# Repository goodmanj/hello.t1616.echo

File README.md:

# hello.t1616.echo
 
This is a version of the ["hello.echo"](http://academy.cba.mit.edu/classes/embedded_programming/index.html#echo) board for Week 6 of Fab Academy, designed for the ATTiny1616 microcontroller.  This particular chip is not included in Neil Gershenfeld's "hello.echo" boards, and we happen to have a lot of them.

Program using Spence Konde's [megaTinyCore](https://github.com/SpenceKonde/megaTinyCore) for Arduino, and a [pyUPDI-style](https://github.com/SpenceKonde/megaTinyCore/blob/master/MakeUPDIProgrammer.md) FTDI-to-UDPI adapter.

Materials:
* 1 uF 1206 SMD capacitor
* SOIC-20W ATTiny1616-S
* 1x6 2.54 mm pitch horizontal male SMD header
* 1x3 2.54 mm pitch horizontal male SMD header

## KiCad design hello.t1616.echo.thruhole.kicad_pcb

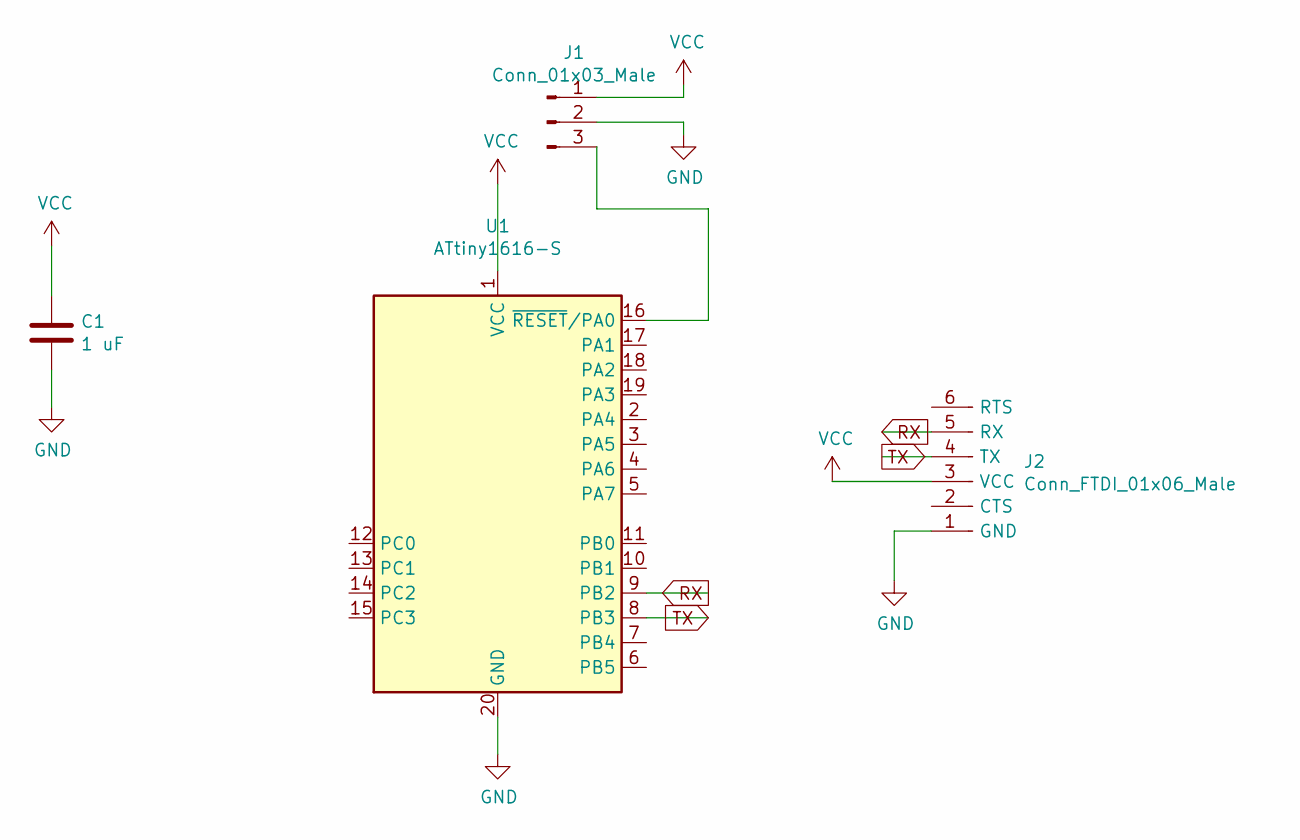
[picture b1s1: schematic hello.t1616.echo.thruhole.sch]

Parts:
C1: 1 uF; fab-C1206
J1: Conn_01x03_Male; PinHeader_1x03_P2.54mm_Horizontal
J2: Conn_FTDI_01x06_Male; PinHeader_1x06_P2.54mm_Horizontal
U1: ATtiny1616-S; SOIC-20W_7.5x12.8mm_P1.27mm

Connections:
GND: C1.2, J1.2, J2.1 (GND), U1.20 (GND)
unnamed: J1.3, U1.16 (~RESET~/PA0)
RX: J2.5 (RX), U1.9 (PB2)
TX: J2.4 (TX), U1.8 (PB3)
VCC: C1.1, J1.1, J2.3 (VCC), U1.1 (VCC)

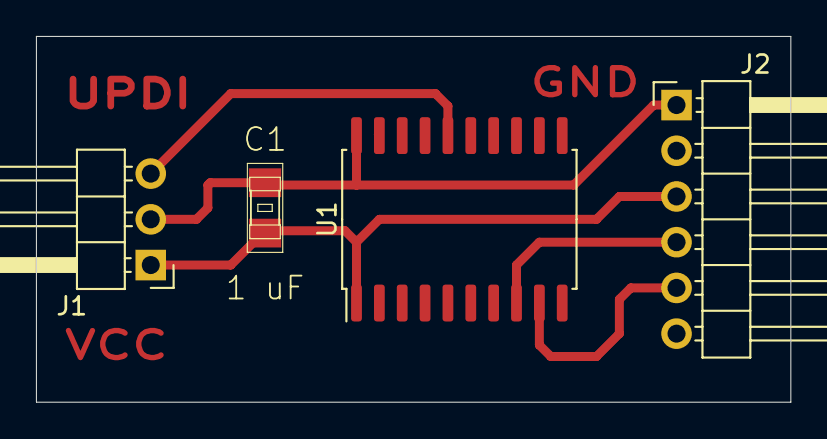
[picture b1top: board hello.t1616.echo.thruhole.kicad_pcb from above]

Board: 2 copper layers, 41.9 x 20.3 mm, 4 parts (0 on the bottom side), 5 nets.

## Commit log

2021-03-02 Finished (?) board
2021-03-02 Surface mount headers, added README.
2021-03-03 Moved serial lines to correct pins.
2021-03-04 Correct part number in echo.
2021-03-04 Added thruhole version
